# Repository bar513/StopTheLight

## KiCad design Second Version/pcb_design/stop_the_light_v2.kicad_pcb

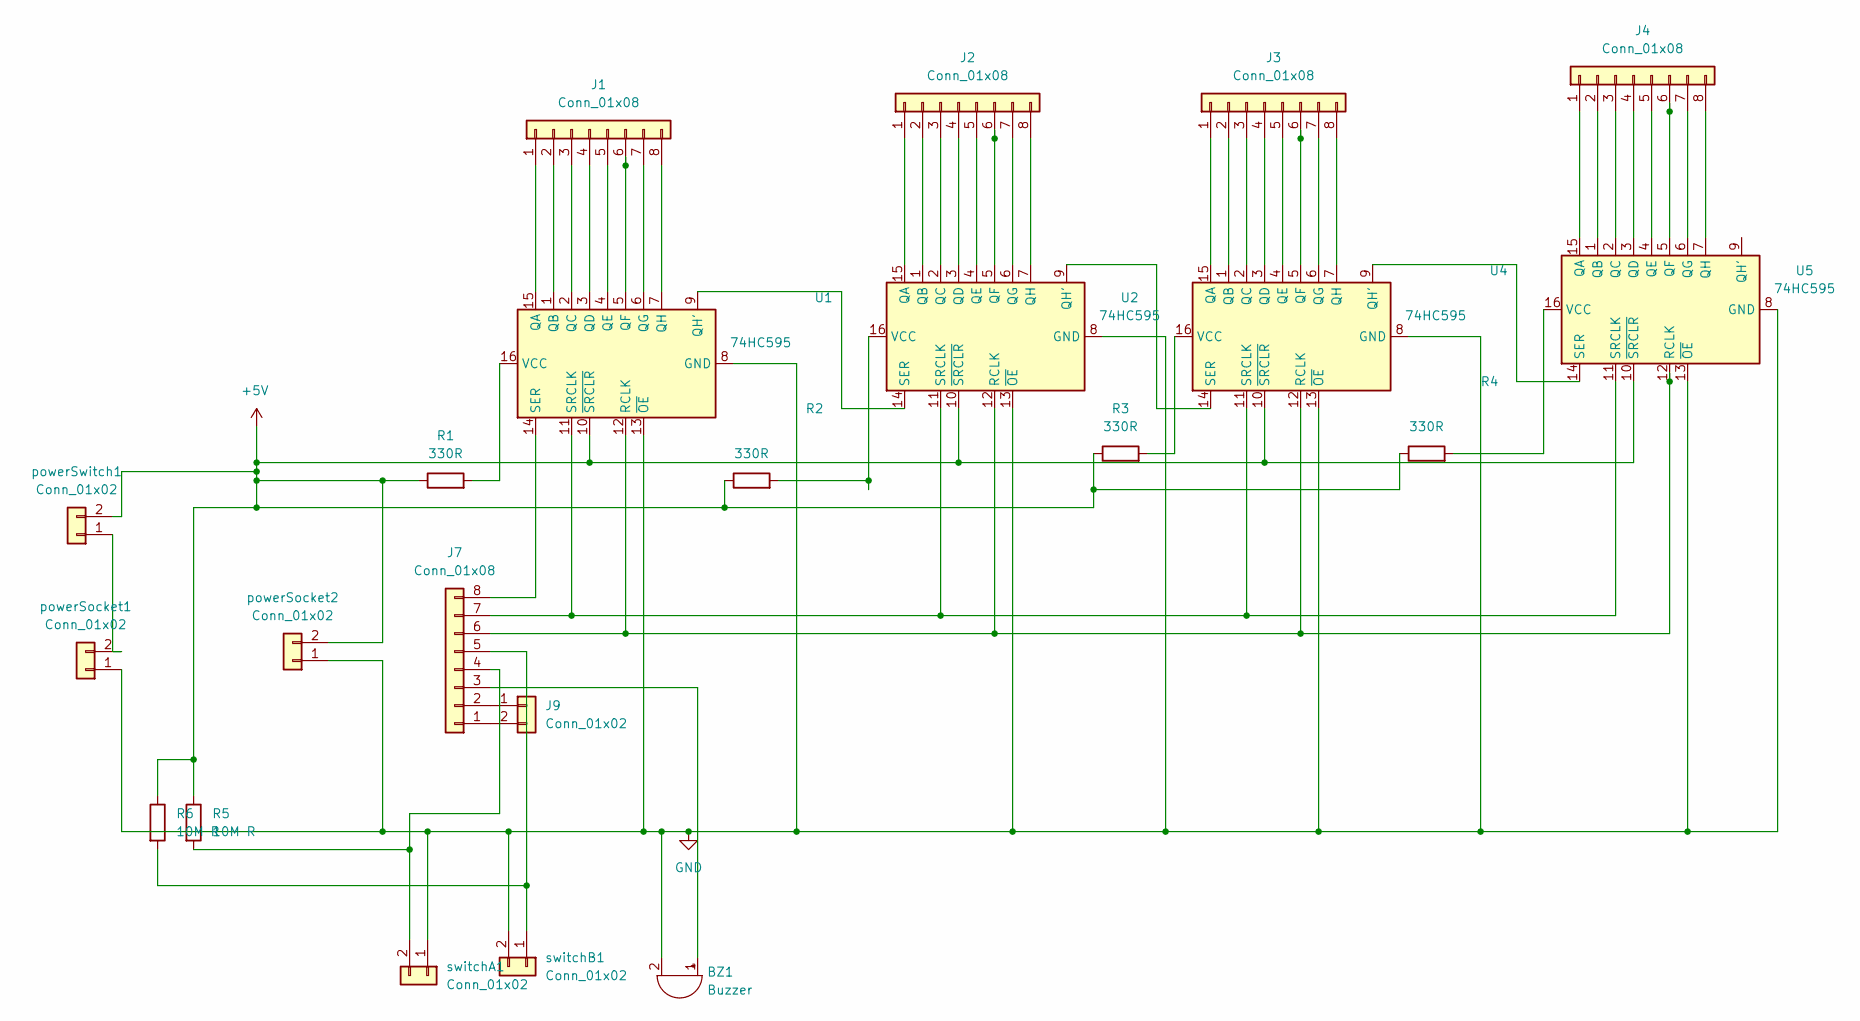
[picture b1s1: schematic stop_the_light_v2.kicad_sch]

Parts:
BZ1: Buzzer; Buzzer_12x9.5RM7.6
J1, J2, J3, J4, J7: Conn_01x08; PinHeader_1x08_P2.54mm_Vertical
J9: Conn_01x02; PinHeader_1x02_P2.54mm_Vertical
R1, R2, R3, R4: 330R; R_Axial_DIN0411_L9.9mm_D3.6mm_P15.24mm_Horizontal
R5, R6: 10M R; R_Axial_DIN0411_L9.9mm_D3.6mm_P15.24mm_Horizontal
U1, U2, U4, U5: 74HC595; DIP-16_W7.62mm_Socket
powerSocket1: Conn_01x02; JST_NV_B02P-NV_1x02_P5.00mm_Vertical
powerSocket2: Conn_01x02; PinHeader_1x02_P2.54mm_Vertical
powerSwitch1: Conn_01x02; PinHeader_1x02_P2.54mm_Vertical
switchA1: Conn_01x02; PinHeader_1x02_P2.54mm_Vertical
switchB1: Conn_01x02; PinHeader_1x02_P2.54mm_Vertical

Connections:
+5V: R1.1, R2.1, R3.1, R4.1, R5.1, R6.1, U1.10 (~SRCLR), U2.10 (~SRCLR), U4.10 (~SRCLR), U5.10 (~SRCLR), powerSocket2.2, powerSwitch1.2
GND: BZ1.2 (-), U1.8 (GND), U1.13 (~OE), U2.8 (GND), U2.13 (~OE), U4.8 (GND), U4.13 (~OE), U5.8 (GND), U5.13 (~OE), powerSocket1.1, powerSocket2.1, switchA1.1, switchB1.2
unnamed: BZ1.1 (+), J7.3
unnamed: J1.1, U1.15 (QA)
unnamed: J1.2, U1.1 (QB)
unnamed: J1.3, U1.2 (QC)
unnamed: J1.4, U1.3 (QD)
unnamed: J1.5, U1.4 (QE)
unnamed: J1.6, U1.5 (QF)
unnamed: J1.7, U1.6 (QG)
unnamed: J1.8, U1.7 (QH)
unnamed: J2.1, U2.15 (QA)
unnamed: J2.2, U2.1 (QB)
unnamed: J2.3, U2.2 (QC)
unnamed: J2.4, U2.3 (QD)
unnamed: J2.5, U2.4 (QE)
unnamed: J2.6, U2.5 (QF)
unnamed: J2.7, U2.6 (QG)
unnamed: J2.8, U2.7 (QH)
unnamed: J3.1, U4.15 (QA)
unnamed: J3.2, U4.1 (QB)
unnamed: J3.3, U4.2 (QC)
unnamed: J3.4, U4.3 (QD)
unnamed: J3.5, U4.4 (QE)
unnamed: J3.6, U4.5 (QF)
unnamed: J3.7, U4.6 (QG)
unnamed: J3.8, U4.7 (QH)
unnamed: J4.1, U5.15 (QA)
unnamed: J4.2, U5.1 (QB)
unnamed: J4.3, U5.2 (QC)
unnamed: J4.4, U5.3 (QD)
unnamed: J4.5, U5.4 (QE)
unnamed: J4.6, U5.5 (QF)
unnamed: J4.7, U5.6 (QG)
unnamed: J4.8, U5.7 (QH)
unnamed: J7.1, J9.2
unnamed: J7.2, J9.1
unnamed: J7.4, R5.2, switchA1.2
unnamed: J7.5, R6.2, switchB1.1
unnamed: J7.6, U1.12 (RCLK), U2.12 (RCLK), U4.12 (RCLK), U5.12 (RCLK)
unnamed: J7.7, U1.11 (SRCLK), U2.11 (SRCLK), U4.11 (SRCLK), U5.11 (SRCLK)
unnamed: J7.8, U1.14 (SER)
unnamed: U1.9 (QH'), U2.14 (SER)
unnamed: R1.2, U1.16 (VCC)
unnamed: U2.9 (QH'), U4.14 (SER)
unnamed: R2.2, U2.16 (VCC)
unnamed: U4.9 (QH'), U5.14 (SER)
unnamed: R3.2, U4.16 (VCC)
unnamed: R4.2, U5.16 (VCC)
unnamed: powerSocket1.2, powerSwitch1.1

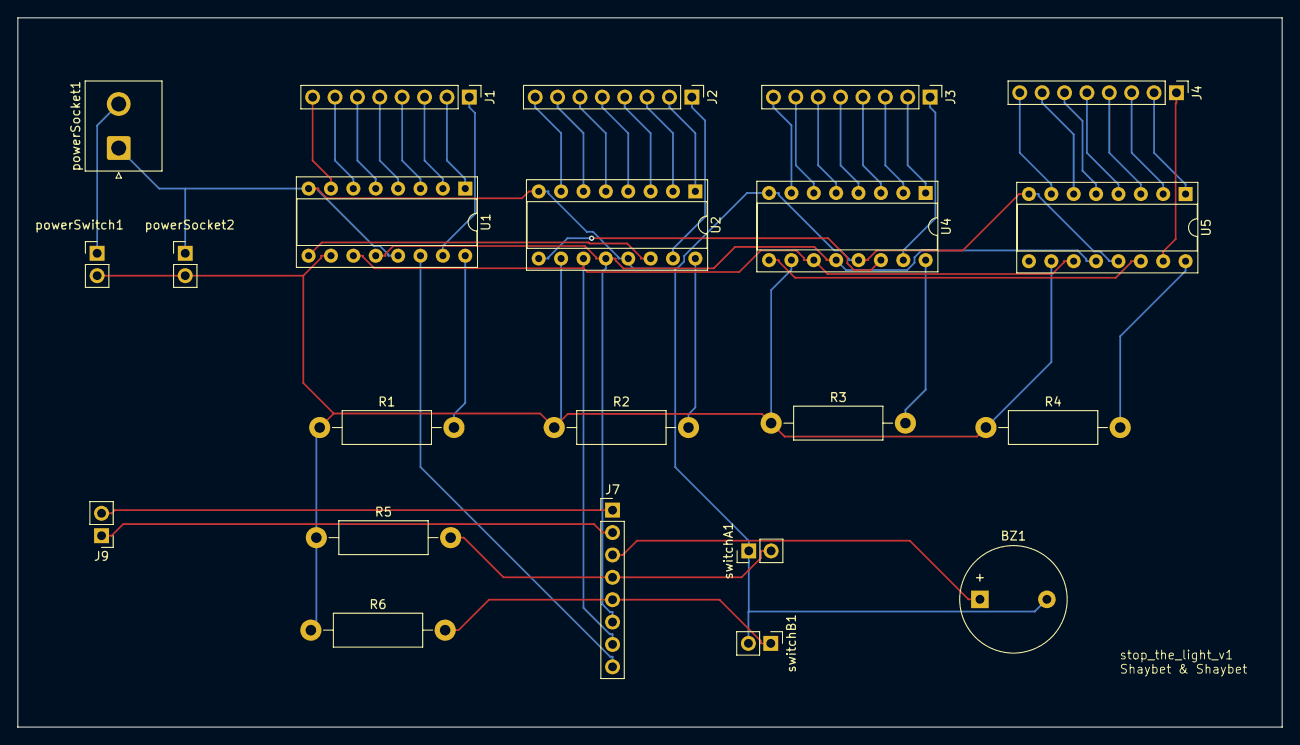
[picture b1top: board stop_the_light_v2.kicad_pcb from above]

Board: 2 copper layers, 143.5 x 80.5 mm, 22 parts (0 on the bottom side), 50 nets.

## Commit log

2024-08-27 Init - test connections, 4 RGBs are blinking
    very naive code of 4 RGBs leds with common cathode that are blinking, each one in its turn.
    This code goal is to check that the RGBs are well connected before we test basic version of the StopTheLightGame.
2024-08-27 POC - V1, Four RGBs are playing after each other
    POC version of the game for one player. 4 RGBs playing in red, when after another and one of them is blue. when button is clicked, the switching stop and the goal is to stop on the blue led.
2024-09-07 Create test_74HC595.ino
    Simple code showing 74HC595 works we leds
2024-09-07 working 2 chained 74HC595 with 16 leds
2024-09-28 Create test_32_leds.ino
    two can play, impossible to loose
2025-02-08 Update test_32_leds.ino
    interrupt and maybe other stuff
2025-02-08 PCB desgin v1
2025-02-08 start show, winning show, restart
    also B button works and score is lowerd as in A
2025-02-15 bug fix - restart speed of winning
2025-02-15 change direction and position each winning session
2025-05-03 nice music for buzzer
2025-05-04 main file with audio, wining and losing point
